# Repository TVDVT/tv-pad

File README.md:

# tv-pad
The tv-pad is a 9 key macropad with an OLED display, and uses QMK firmware.
It's main purpose it to help with note taking on 2 in 1 laptops, but can be reprogrammed with any keys.

This project was made for Hack Club Stardance!

# Demo
https://youtube.com/shorts/lUIq6G4Zl5c?si=yzHyjfCIUw9PWCoL

# Features:
- 9 keys
- 128x32 OLED display

# CAD Model:
Everything fits together using 4 M3 Bolts and heatset inserts. It has 2 separate printed parts: top and bottom. I used Onshape.

# Case:

# PCB:
I used KiCad for the PCB:
Schematic

PCB

# Firmware:
I used QMK for the firmware.

# Bill of Materials (BOM)

| Qty | Part | Supplier | Cost (USD) | Link |
|-----|------|----------|------------|------|
| 9 | Cherry MX Switches | AliExpress | $0.69 | https://www.aliexpress.com/item/1005009946528694.html |
| 9 | DSA Keycaps | AliExpress | $1.01 | https://www.aliexpress.com/item/1005013381162174.html |
| 1 | 0.91 in 128x32 OLED Display | AliExpress | $8.71 | https://www.aliexpress.com/item/1005008640108394.html |
| 4 | M3x5x4mm Heatset Inserts | AliExpress | $0.48 | https://www.aliexpress.com/item/1005011959188413.html |
| 4 | M3x16mm SHCS Bolts | AliExpress | $0.40 | https://www.aliexpress.com/item/1005012367821308.html |
| 6 | 1N4148 DO-35 Diodes | AliExpress | $0.72 | https://www.aliexpress.com/item/1005009379098965.html |
| 1 | Seeed XIAO RP2040 | AliExpress | $4.99 | https://www.aliexpress.com/item/1005013232776575.html |
| 1 | Case (2 Printed Parts) | Printing Legion | |  |
|  |  | **Total (excluding case)** | **$17.00** |  |

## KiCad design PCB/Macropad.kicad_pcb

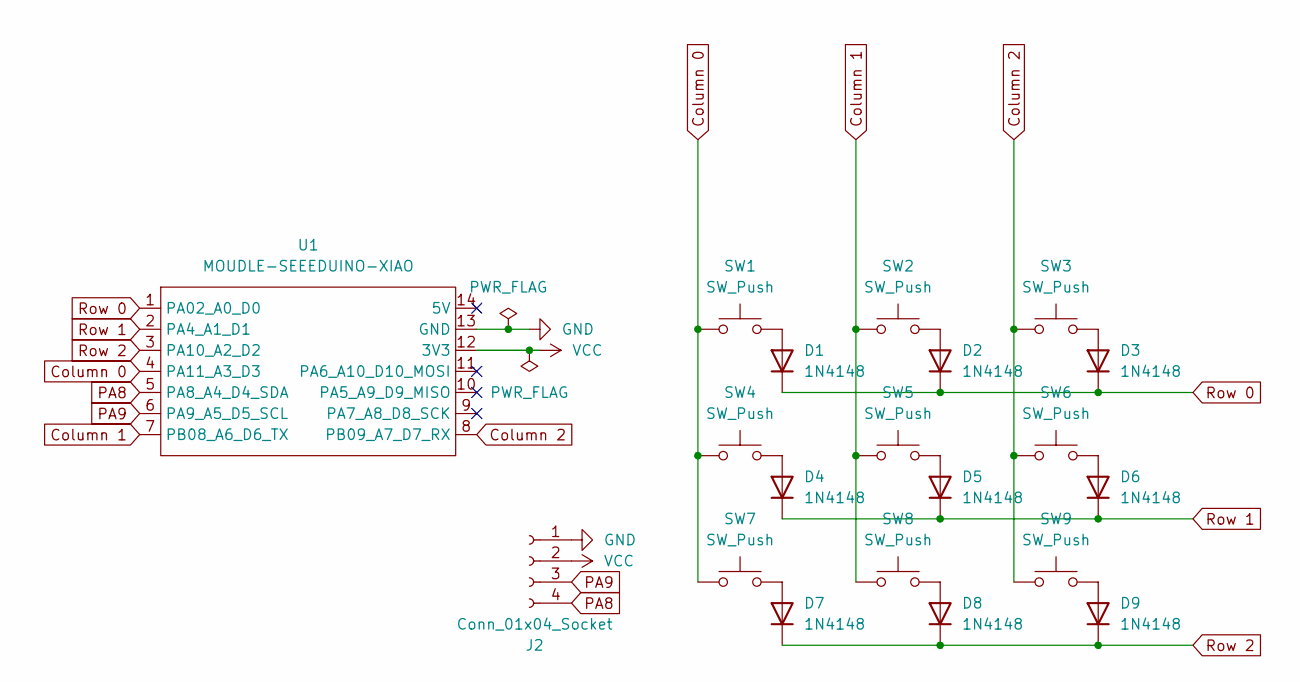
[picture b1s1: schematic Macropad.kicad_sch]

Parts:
D1, D2, D3, D4, D5, D6, D7, D8, D9: 1N4148; D_DO-35_SOD27_P7.62mm_Horizontal
J2: Conn_01x04_Socket; SSD1306-0.91-OLED-4pin-128x32
SW1, SW2, SW3, SW4, SW5, SW6, SW7, SW8, SW9: SW_Push; SW_Cherry_MX_1.00u_PCB
U1: MOUDLE-SEEEDUINO-XIAO; XIAO-Generic-Hybrid-14P-2.54-21X17.8MM

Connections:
Column 0: SW1.1, SW4.1, SW7.1, U1.4 (PA11_A3_D3)
Column 1: SW2.1, SW5.1, SW8.1, U1.7 (PB08_A6_D6_TX)
Column 2: SW3.1, SW6.1, SW9.1, U1.8 (PB09_A7_D7_RX)
GND: J2.1, U1.13 (GND)
unnamed: D1.2 (A), SW1.2
unnamed: D2.2 (A), SW2.2
unnamed: D3.2 (A), SW3.2
unnamed: D4.2 (A), SW4.2
unnamed: D5.2 (A), SW5.2
unnamed: D6.2 (A), SW6.2
unnamed: D7.2 (A), SW7.2
unnamed: D8.2 (A), SW8.2
unnamed: D9.2 (A), SW9.2
PA8: J2.4, U1.5 (PA8_A4_D4_SDA)
PA9: J2.3, U1.6 (PA9_A5_D5_SCL)
Row 0: D1.1 (K), D2.1 (K), D3.1 (K), U1.1 (PA02_A0_D0)
Row 1: D4.1 (K), D5.1 (K), D6.1 (K), U1.2 (PA4_A1_D1)
Row 2: D7.1 (K), D8.1 (K), D9.1 (K), U1.3 (PA10_A2_D2)
VCC: J2.2, U1.12 (3V3)

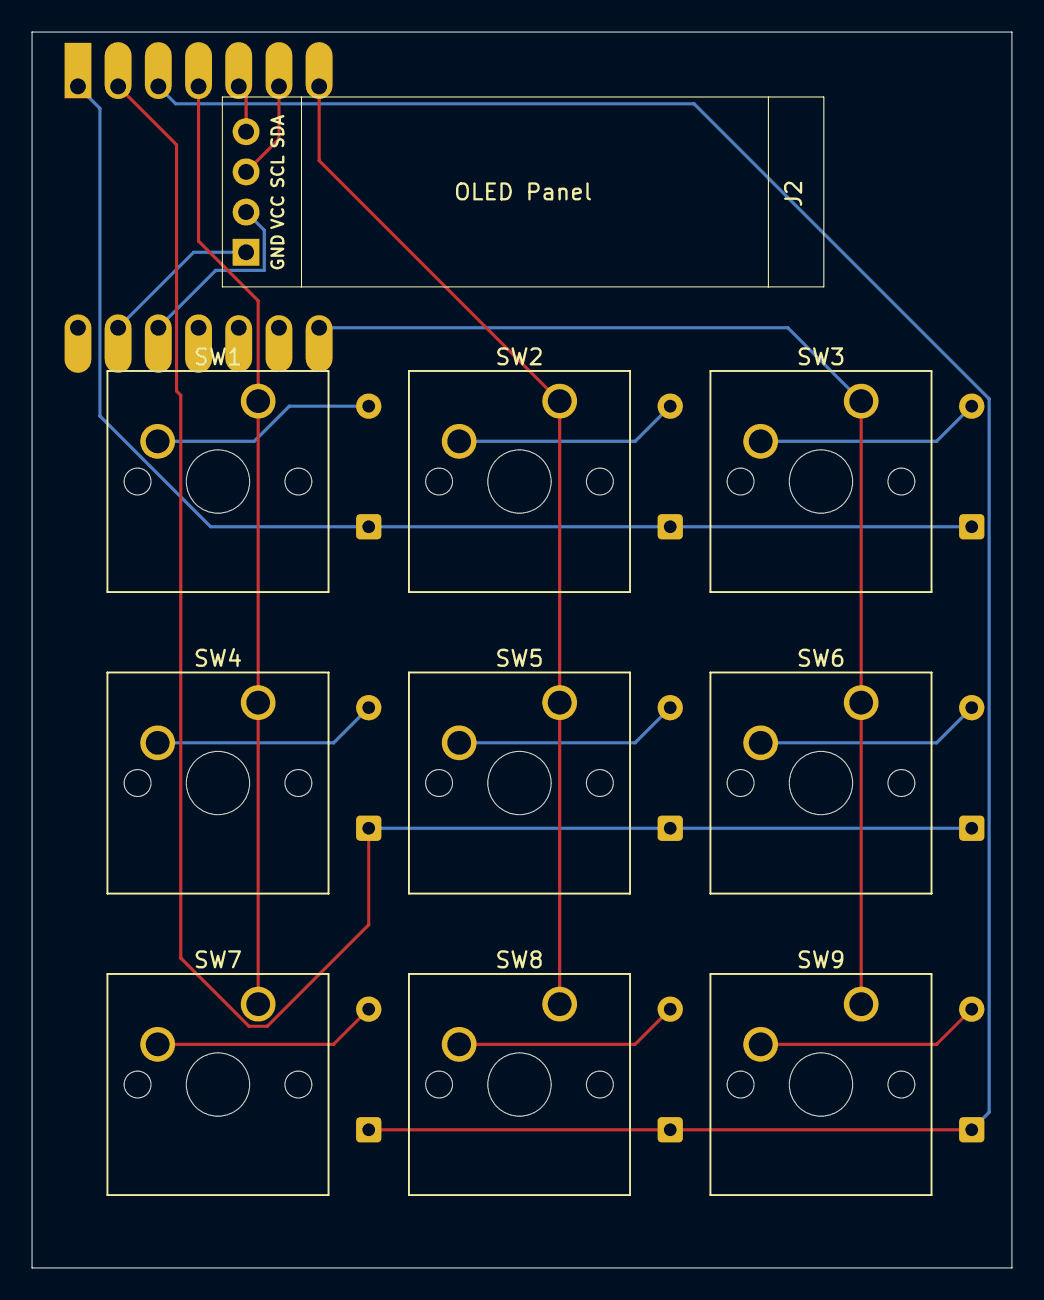
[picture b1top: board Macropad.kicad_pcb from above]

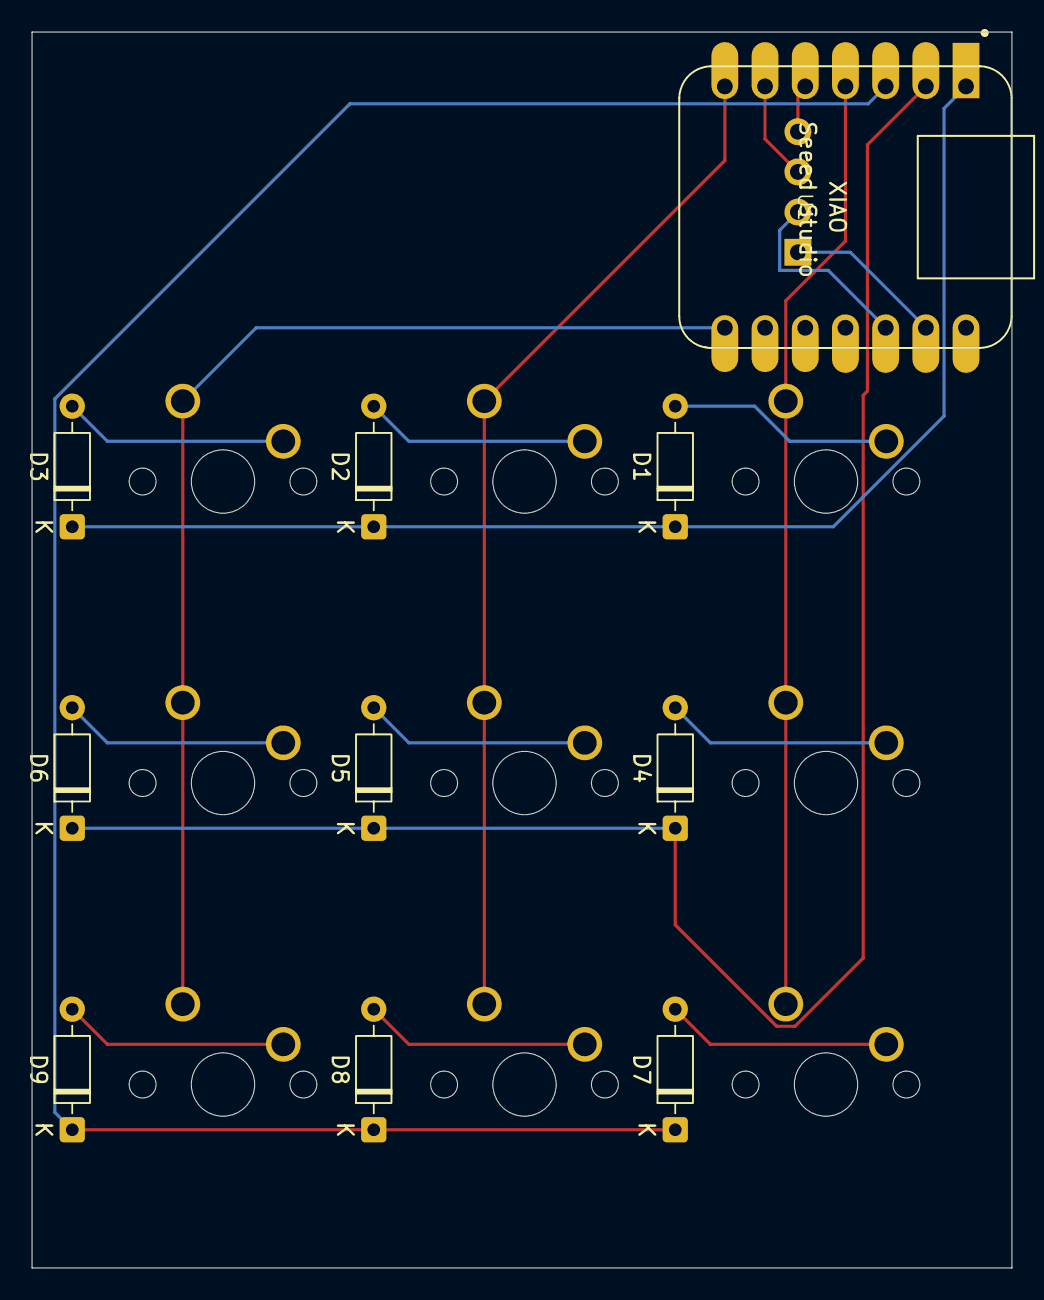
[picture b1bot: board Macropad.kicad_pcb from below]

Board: 2 copper layers, 61.9 x 78.1 mm, 20 parts (10 on the bottom side), 19 nets.
